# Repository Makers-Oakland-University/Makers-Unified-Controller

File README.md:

# Makers Unified Controller

The Makers at OU unified controller is a simple controller based on the ESP32 designed to be a one-size fits all controller for robotics projects and interactive exhibits. 
It is designed to be low cost, simple to assemble, and versatile to suit any project requirements. 
Programming and charging are accomplished by the available micro-usb plug, the battery can also be changed by the user. 

## Contents
This repo contains the EDA and CAD files for the controller created with [KiCad](https://www.kicad.org/) and [FreeCAD](https://www.freecadweb.org/) respectively. 
Both tools are open source and freely available 

## Contributing
For any new changes to the controller after version 1 please create a branch of pull request for any major design changes to the controller. 

## License
[MIT](https://choosealicense.com/licenses/mit/)

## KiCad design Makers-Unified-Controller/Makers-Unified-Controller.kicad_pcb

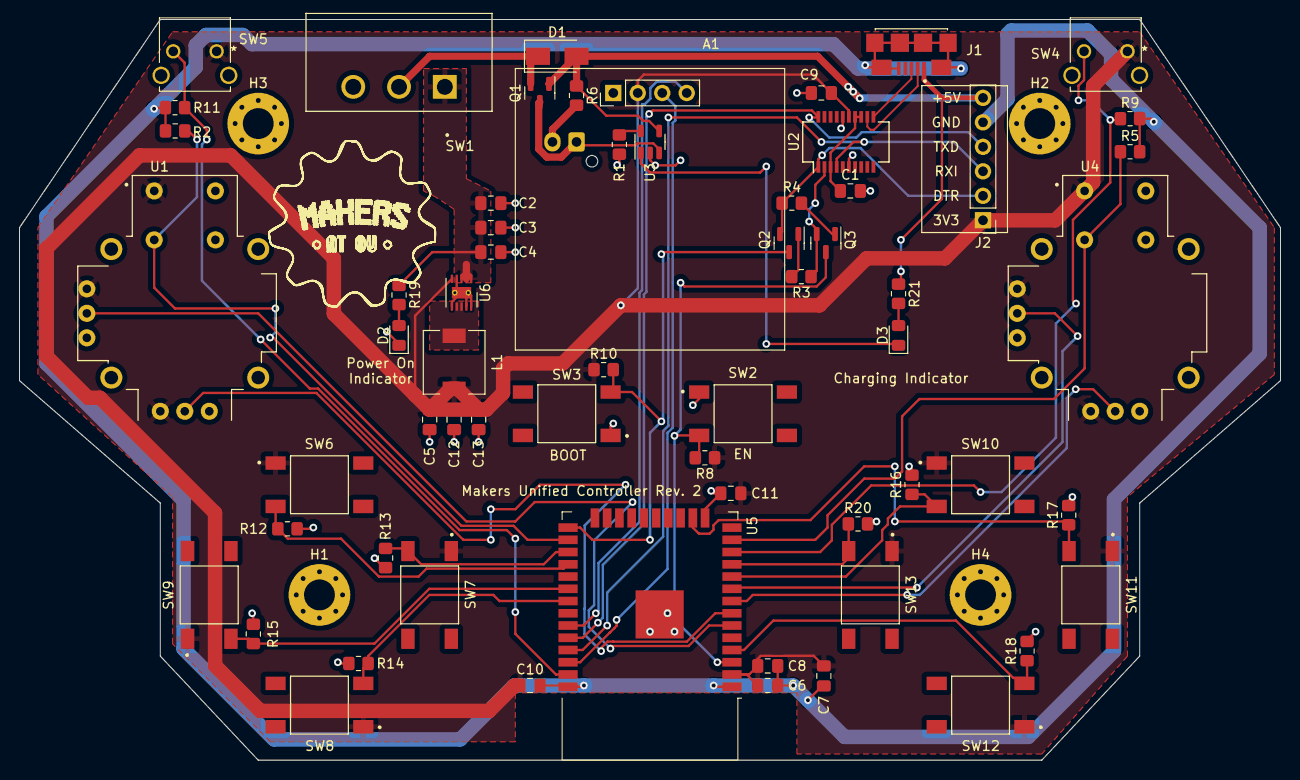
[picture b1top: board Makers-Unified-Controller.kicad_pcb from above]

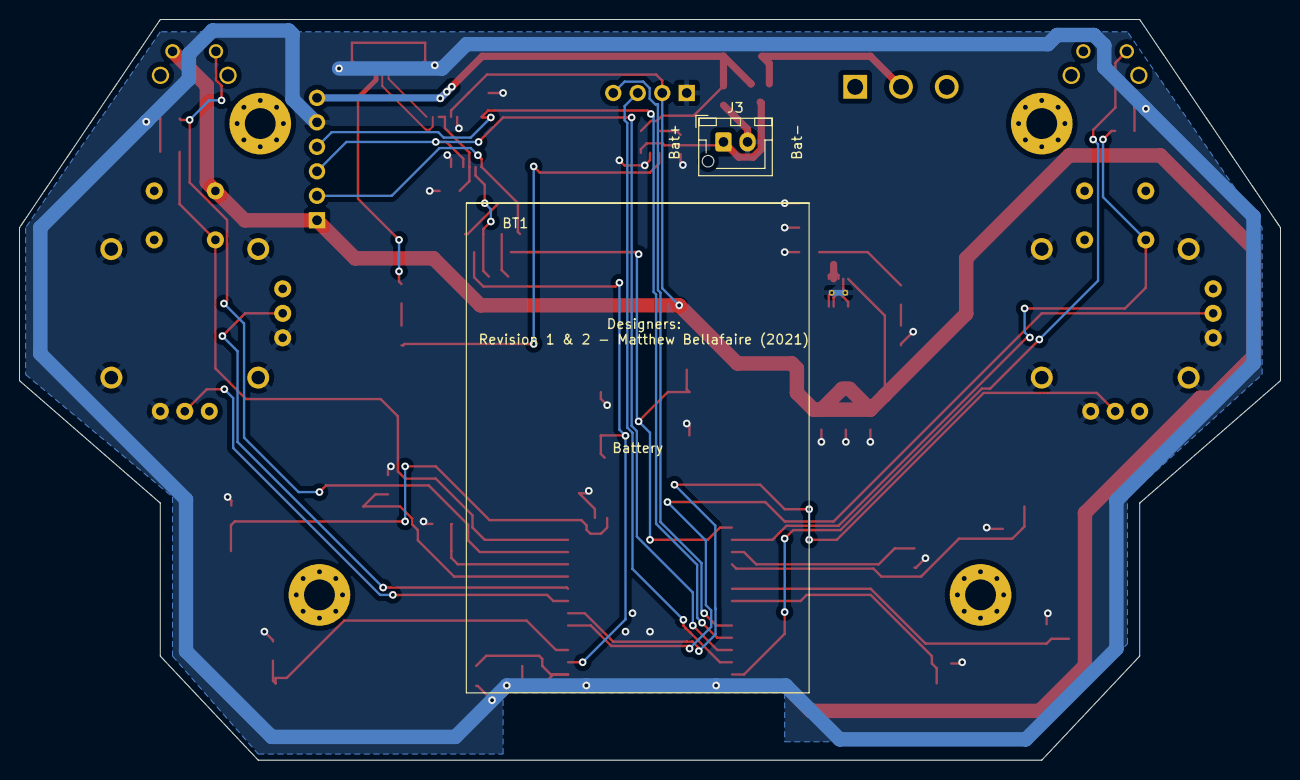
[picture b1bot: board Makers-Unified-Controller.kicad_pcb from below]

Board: 2 copper layers, 130.8 x 76.8 mm, 68 parts (2 on the bottom side), 40 nets.

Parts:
A1: SSD1306
BT1: PRT-18286; PRT18286
C1, C6: 0.1u; C_0805_2012Metric_Pad1.18x1.45mm_HandSolder
C2, C3, C5, C7, C12: 10u; C_0805_2012Metric_Pad1.18x1.45mm_HandSolder
C4, C8, C9, C10, C11, C13: 1u; C_0805_2012Metric_Pad1.18x1.45mm_HandSolder
D1: CDBA340-G; D_SMA
D2: G_LED; LED_0805_2012Metric_Pad1.15x1.40mm_HandSolder
D3: B_LED; LED_0805_2012Metric_Pad1.15x1.40mm_HandSolder
H1, H2, H3, H4: MountingHole; MountingHole_3.2mm_M3_Pad_Via
J1: USB_B_Micro; AMPHENOL_10118192-0002LF
J2: backup_PROG; backup_prog_header
J3: BAT Connector; PRT-18286 Connector
L1: 6.2u; L_6.3x6.3_H3
Q1: PJA3401A_R1_00001; SOT-23
Q2, Q3: MMBT3904; SOT-23
R1, R19, R21: 2.2k; R_0805_2012Metric_Pad1.20x1.40mm_HandSolder
R2, R3, R4, R5, R6, R8, R9, R10, R11, R12, R13, R14, R15, R16, R17, R18, R20: 10k; R_0805_2012Metric_Pad1.20x1.40mm_HandSolder
SW1: SW_DPDT_x2; SW_L102021ML04Q
SW2, SW3, SW6, SW7, SW8, SW9, SW10, SW11, SW12, SW13: SW_Push; SW_1571563-4
SW4, SW5: SW_RIGHT_ANGLE; 1825027-8
U1, U4: COM-09032; XDCR_COM-09032
U2: FT231XS; SSOP-20_3.9x8.7mm_P0.635mm
U3: MCP73832-2-0T; SOT-23-5
U5: ESP32-WROOM-32D; ESP32-WROOM-32
U6: TPS62046DRCR; VSON-10-1EP_3x3mm_P0.5mm_EP1.2x2mm_ThermalVias

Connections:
+3V3: A1.2 (VDD), C5.1, C6.1, C7.1, C8.1, C9.1, C10.1, C11.1, C12.1, C13.1, J2.1, L1.2, R8.1, R10.1, SW4.1, SW5.1, SW6.1, SW7.1, SW8.1, SW9.1, SW10.1, SW11.1, SW12.1, SW13.1, U1.B1A (SW+), U1.H1 (H+), U1.V1 (V+), U2.15 (VCC), U4.B1A (SW+), U4.H1 (H+), U4.V1 (V+), U5.2 (VDD), U6.5 (FB)
+5V: D1.2 (A), J1.1 (VBUS), J2.6, Q1.1 (G), R6.1, R21.1, U3.4 (VDD)
/BAT+: J3.1, Q1.3 (D), U3.3 (VBAT)
/BRIDGE_DTR: J2.2, Q2.2 (E), R4.1, U2.1 (~DTR)
/BRIDGE_RTS: Q3.2 (E), R3.1, U2.2 (~RTS)
/BRIDGE_RX: J2.3, U2.4 (RXD), U5.35 (TXD0/IO1)
/BRIDGE_TX: J2.4, U2.20 (TXD), U5.34 (RXD0/IO3)
/CHG_COMPLETE: D3.1 (K), U3.1 (STAT)
/D+: J1.3 (D+), U2.11 (USBDP)
/D-: J1.2 (D-), U2.12 (USBDM)
/EN: Q3.3 (C), R8.2, SW2.3, U5.3 (EN)
/I2C_SCL: A1.3 (SCL), U5.36 (IO22)
/I2C_SDA: A1.4 (SDA), U5.33 (IO21)
/IO0: Q2.3 (C), R10.2, SW3.3, U5.25 (IO0)
/LEFT_JOY_SW: R2.1, U1.B2A (SW-), U5.26 (IO4)
/LEFT_JOY_X: U1.H2 (H), U5.7 (IO35)
/LEFT_JOY_Y: U1.V2 (V), U5.6 (IO34)
/PWR_IN: C2.1, C3.1, C4.1, R19.1, SW1.1 (A), U6.1 (EN), U6.2 (VIN), U6.3 (VIN)
/Power Management/BUCK_SW: L1.1, U6.7 (SW), U6.8 (SW)
/RIGHT_JOY_SW: R5.1, U4.B2A (SW-), U5.13 (IO14)
/RIGHT_JOY_X: U4.H2 (H), U5.8 (IO32)
/RIGHT_JOY_Y: U4.V2 (V), U5.9 (IO33)
/SW_1: R12.1, SW6.3, U5.28 (IO17)
/SW_2: R13.1, SW7.3, U5.27 (IO16)
/SW_3: R14.1, SW8.3, U5.31 (IO19)
/SW_4: R15.1, SW9.3, U5.30 (IO18)
/SW_5: R16.1, SW10.3, U5.10 (IO25)
/SW_6: R17.1, SW11.3, U5.16 (IO13)
/SW_7: R18.1, SW12.3, U5.4 (SENSOR_VP)
/SW_8: R20.1, SW13.3, U5.11 (IO26)
/TRIG_L: R11.1, SW5.2, U5.37 (IO23)
/TRIG_R: R9.1, SW4.2, U5.12 (IO27)
GND: A1.1 (GND), C1.2, C2.2, C3.2, C4.2, C5.2, C6.2, C7.2, C8.2, C9.2, C10.2, C11.2, C12.2, C13.2, D2.1 (K), J1.5 (GND), J1.6 (Shield), J2.5, J3.2, R1.2, R2.2, R5.2, R6.2, R9.2, R11.2, R12.2, R13.2, R14.2, R15.2, R16.2, R17.2, R18.2, R20.2, SW2.1, SW3.1, U1.H3 (H-), U1.S1 (SHIELD), U1.S2 (SHIELD), U1.S3 (SHIELD), U1.S4 (SHIELD), U1.V3 (V-), U2.6 (GND), U2.16 (GND), U3.2 (VSS), U4.H3 (H-), U4.S1 (SHIELD), U4.S2 (SHIELD), U4.S3 (SHIELD), U4.S4 (SHIELD), U4.V3 (V-), U5.1 (GND), U5.15 (GND), U5.38 (GND), U5.39 (GND), U6.4 (GND), U6.6 (MODE), U6.9 (PGND), U6.10 (PGND), U6.11 (PAD)
unnamed: C1.1, U2.3 (VCCIO), U2.13 (3V3OUT), U2.14 (~RESET)
unnamed: D1.1 (K), Q1.2 (S), SW1.2 (B)
unnamed: D2.2 (A), R19.2
unnamed: D3.2 (A), R21.2
unnamed: Q2.1 (B), R3.2
unnamed: Q3.1 (B), R4.2
unnamed: R1.1, U3.5 (PROG)

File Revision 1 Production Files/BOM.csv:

Qty,Reference(s),Value,LibPart,Footprint,Datasheet,digikey_part_number
1,A1,SSD1306,Project_Imports:SSD1306,Footprint_Imports:SSD1306,,
1,BT1,BC4AAW,Project_Imports:BC4AAW,Footprint_Imports:BAT_BC4AAW,,BC4AAW-ND
5,"C1, C6",0.1u,Device:C,Capacitor_SMD:C_0805_2012Metric_Pad1.18x1.45mm_HandSolder,~,1276-1099-1-ND
5,"C2, C4, C7",10u,Device:C,Capacitor_SMD:C_0805_2012Metric_Pad1.18x1.45mm_HandSolder,~,1276-6455-1-ND
10,"C3, C5, C8, C9, C10, C11",1u,Device:C,Capacitor_SMD:C_0805_2012Metric_Pad1.18x1.45mm_HandSolder,~,1276-1275-1-ND
3,D1,CDBA340-G,Device:D_Schottky,Diode_SMD:D_SMA,https://media.digikey.com/pdf/Data%20Sheets/Comchip%20PDFs/C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,641-1101-1-ND
3,D2,G_LED,Device:LED,LED_SMD:LED_0805_2012Metric_Pad1.15x1.40mm_HandSolder,~,160-1218-1-ND
3,D3,B_LED,Device:LED,LED_SMD:LED_0805_2012Metric_Pad1.15x1.40mm_HandSolder,~,732-4982-1-ND
4,"H1, H2, H3, H4",MountingHole,Mechanical:MountingHole,MountingHole:MountingHole_3.2mm_M3_Pad_Via,~,
3,J1,USB_B_Micro,Connector:USB_B_Micro,Footprint_Imports:AMPHENOL_10118192-0002LF,https://www.amphenol-icc.com/media/wysiwyg/files/drawing/101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,609-5379-1-ND
1,J2,backup_PROG,Connector:Conn_01x06_Female,Footprint_Imports:backup_prog_header,~,
3,L1,4.7u,Device:L,Footprint_Imports:NRS5024T4R7MMGJ,,587-5937-1-ND
3,Q1,SI2305B-TP,Transistor_FET:FDN340P,Package_TO_SOT_SMD:SOT-23,https://www.mccsemi.com/pdf/Products/SI2305B(SOT-23).pdf,SI2305B-TPMSCT-ND
5,"Q2, Q3",MMBT3904,Transistor_BJT:MMBT3904,Package_TO_SOT_SMD:SOT-23,https://www.onsemi.com/pub/Collateral/2N3903-D.PDF,3757-MMBT3904_R1_00001CT-ND
25,"R1, R2, R3, R4, R5, R7, R8, R9, R10, R11, R12, R13, R14, R15, R16, R17, R18, R20",10k,Device:R,Resistor_SMD:R_0805_2012Metric_Pad1.20x1.40mm_HandSolder,~,RMCF0805JT10K0CT-ND
3,R6,47k,Device:R,Resistor_SMD:R_0805_2012Metric_Pad1.20x1.40mm_HandSolder,~,RMCF0805JT47K0CT-ND
5,"R19, R21",470,Device:R,Resistor_SMD:R_0805_2012Metric_Pad1.20x1.40mm_HandSolder,~,A126441CT-ND
1,SW1,SW_DPDT_x2,Switch:SW_DPDT_x2,Footprint_Imports:SW_L102021ML04Q,https://www.ckswitches.com/media/1423/l.pdf,CKC5102-ND
15,"SW2, SW3, SW6, SW7, SW8, SW9, SW10, SW11, SW12, SW13",SW_Push,Project_Imports:1571563-4,Footprint_Imports:SW_1571563-4,https://www.te.com/commerce/DocumentDelivery/DDEController?A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,450-2055-1-ND
5,"SW4, SW5",SW_RIGHT_ANGLE,Switch:SW_Push,Footprint_Imports:1825027-8,https://www.te.com/commerce/DocumentDelivery/DDEController?A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,450-1657-ND
2,"U1, U4",COM-09032,Project_Imports:COM-09032,Footprint_Imports:XDCR_COM-09032,,1568-1526-ND
1,U2,FT231XQ,Interface_USB:FT231XQ,Package_DFN_QFN:QFN-20-1EP_4x4mm_P0.5mm_EP2.5x2.5mm,https://www.ftdichip.com/Support/Documents/DataSheets/ICs/DS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,
1,U3,TLV62568DBV,Regulator_Switching:TLV62568DBV,Package_TO_SOT_SMD:SOT-23-5,http://www.ti.com/lit/ds/symlink/tlv62568.pdf,296-47387-1-ND
1,U5,ESP32-WROOM-32D,RF_Module:ESP32-WROOM-32D,RF_Module:ESP32-WROOM-32,https://www.espressif.com/sites/default/files/documentation/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,1965-ESP32-WROOM-32D(4MB)CT-ND

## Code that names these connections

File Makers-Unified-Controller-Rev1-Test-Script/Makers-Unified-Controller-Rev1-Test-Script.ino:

/* Test script for makers unified controller. 
    Author: Matthew Bellafaire
    Date: December 17th, 2021

    This script is designed to test that a controller is properly assembled and show that all buttons
    and joysticks are read properly. The buttons and joystick values are displayed on the SSD1306 display. 
    This script requires the SSD1306 Adafruit library along with the Adafruit GFX library, both of which
    can be installed through the library manager by navigating to tools > manage libraries. 
*/

#include <Wire.h>

#include <Adafruit_GFX.h>

#include <Adafruit_SSD1306.h>

//function signitures
void initIO();
void drawTestData();

//screen size
#define SCREEN_WIDTH 128
#define SCREEN_HEIGHT 64

//button defines (probably going to want to copy these to any other script for the controller)
#define LEFT_JOY_Y 13
#define LEFT_JOY_X 14
#define LEFT_JOY_SW 4

#define RIGHT_JOY_X 32
#define RIGHT_JOY_Y 33
#define RIGHT_JOY_SW 35

#define SW1 17
#define SW2 16
#define SW3 19
#define SW4 18
#define SW5 25
#define SW6 34
#define SW7 36
#define SW8 26

#define LEFT_TRIG 23
#define RIGHT_TRIG 27

//array for simplification of button reading code. 
int buttons[] = {
  SW1,
  SW2,
  SW3,
  SW4,
  SW5,
  SW6,
  SW7,
  SW8,
  LEFT_TRIG,
  RIGHT_TRIG,
  LEFT_JOY_SW,
  RIGHT_JOY_SW
};

//init display.
Adafruit_SSD1306 display(SCREEN_WIDTH, SCREEN_HEIGHT, & Wire, -1);

void setup() {
  Serial.begin(115200);

  //wait for display.
  if (!display.begin(SSD1306_SWITCHCAPVCC, 0x3C)) { // Address 0x3D for 128x64
    Serial.println(F("SSD1306 allocation failed"));
    for (;;);
  }

  //initialize IO
  initIO();

  delay(500);
  display.clearDisplay();
}

void loop() {
  //read read every button and joystick then draw the results to the screen.
  drawTestData();
}

void initIO() {
  pinMode(LEFT_JOY_Y, INPUT);
  pinMode(LEFT_JOY_X, INPUT);
  pinMode(LEFT_JOY_SW, INPUT);

  pinMode(RIGHT_JOY_Y, INPUT);
  pinMode(RIGHT_JOY_X, INPUT);
  pinMode(RIGHT_JOY_SW, INPUT);

  pinMode(SW1, INPUT);
  pinMode(SW2, INPUT);
  pinMode(SW3, INPUT);
  pinMode(SW4, INPUT);
  pinMode(SW5, INPUT);
  pinMode(SW6, INPUT);
  pinMode(SW7, INPUT);
  pinMode(SW8, INPUT);

  pinMode(LEFT_TRIG, INPUT);
  pinMode(RIGHT_TRIG, INPUT);
}

#define BUTTON_DISPLAY_GRID_SIZE SCREEN_WIDTH / 6

//reads each button and joystick and displays the value on the display. 
//buttons that are pressed will show a label on the screen, whereas buttons that are not
//will show nothing. 
void drawTestData() {

  //clear display
  display.clearDisplay();

  display.setTextColor(WHITE);
  display.setCursor(0, 0);

  //makers :)
  display.println("Makers @ OU");

  //loop through each button in the array, arrange them onto a 6x2 grid
  for (int a = 0; a < 12; a++) {

    //move to grid position
    display.setCursor((a % 6) * BUTTON_DISPLAY_GRID_SIZE, 10 + (10 * (a / 6)));

    //if button is pressed display white, otherwise display black.
    if (digitalRead(buttons[a])) {
      display.setTextColor(WHITE);
    } else {
      display.setTextColor(BLACK);
    }

    //print button with above formatting and location.
    display.print("S" + String(a + 1));

  }

  //read joysticks. 
  display.setTextColor(WHITE);

  //left joystick
  display.setCursor(0, 30);
  display.print("Left x:" + String(analogRead(LEFT_JOY_X)) + " y:" + String(analogRead(LEFT_JOY_Y)));

  //right joystick
  display.setCursor(0, 40);
  display.print("Right x:" + String(analogRead(RIGHT_JOY_X)) + " y:" + String(analogRead(RIGHT_JOY_Y)));

  //push to display.
  display.display();

}

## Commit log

2021-12-04 readme
2021-12-05 Initial Kicad Design - needs parts sources, footprints, and layout
2021-12-05 Completed schematic
2021-12-05 Rough Component layout
2021-12-05 Compacted layout
2021-12-06 Routed critical signals and power
2021-12-06 buck converter routing
2021-12-07 Completed Routing
2021-12-07 Exported production files for rev 1 to "Revision 1 Production Files"
2021-12-16 started cad work for controller
2021-12-17 created test script for the controller to validate assembly.
2022-04-01 TODO for revision 2 notes
2022-06-18 Completed Update of Schematic to Revision 2
2022-06-18 Started PCB - removed unused components from revision 1
2022-06-18 fixed BOM item in schematic
2022-06-19 Completed routing - TODO final checks
2022-06-21 Finalized layout and exported files
2022-06-21 minor edits
2022-07-13 added interactive BOM
2022-07-20 minor edits to schematic and Ibom

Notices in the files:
parts and their libraries:
Copyright 2021 Accelerated Designs. All rights reserved.
